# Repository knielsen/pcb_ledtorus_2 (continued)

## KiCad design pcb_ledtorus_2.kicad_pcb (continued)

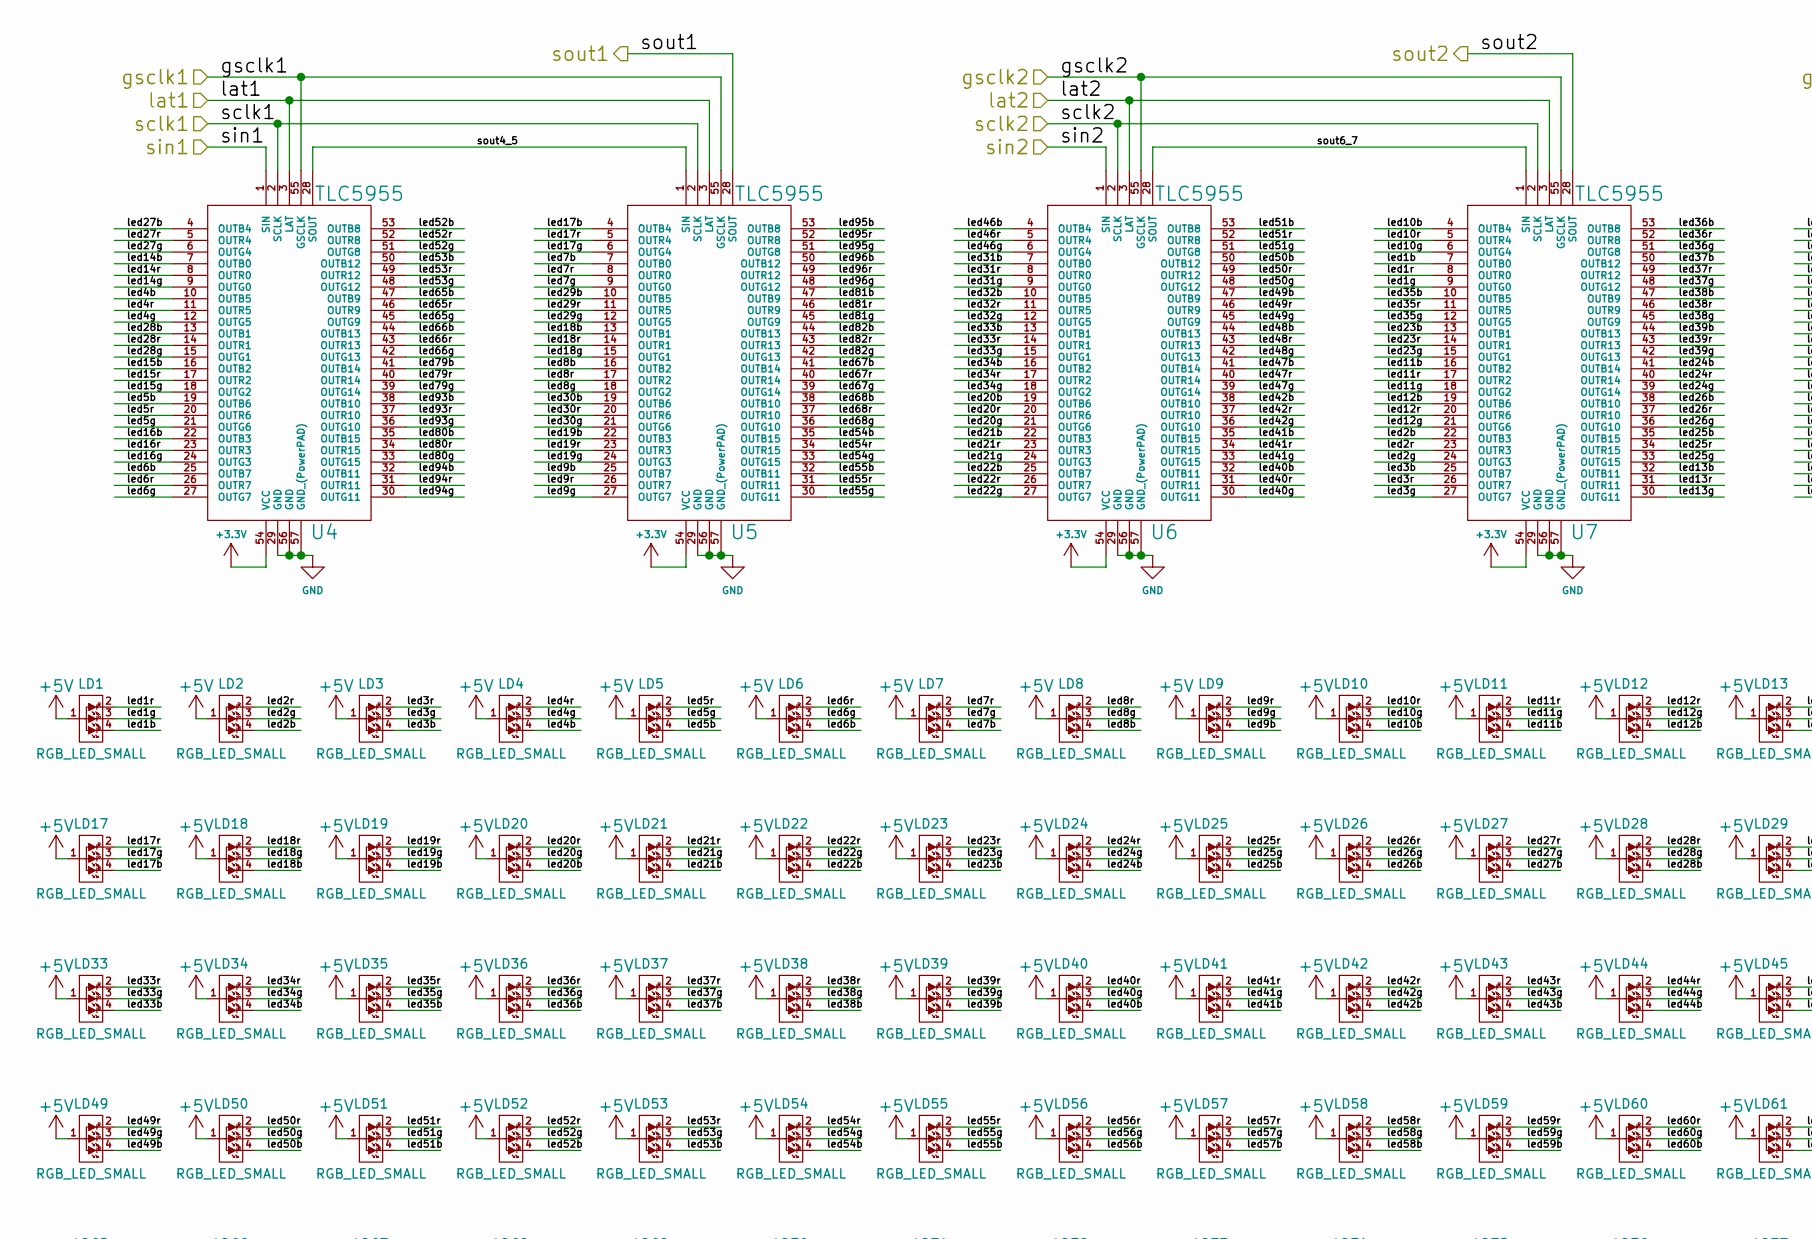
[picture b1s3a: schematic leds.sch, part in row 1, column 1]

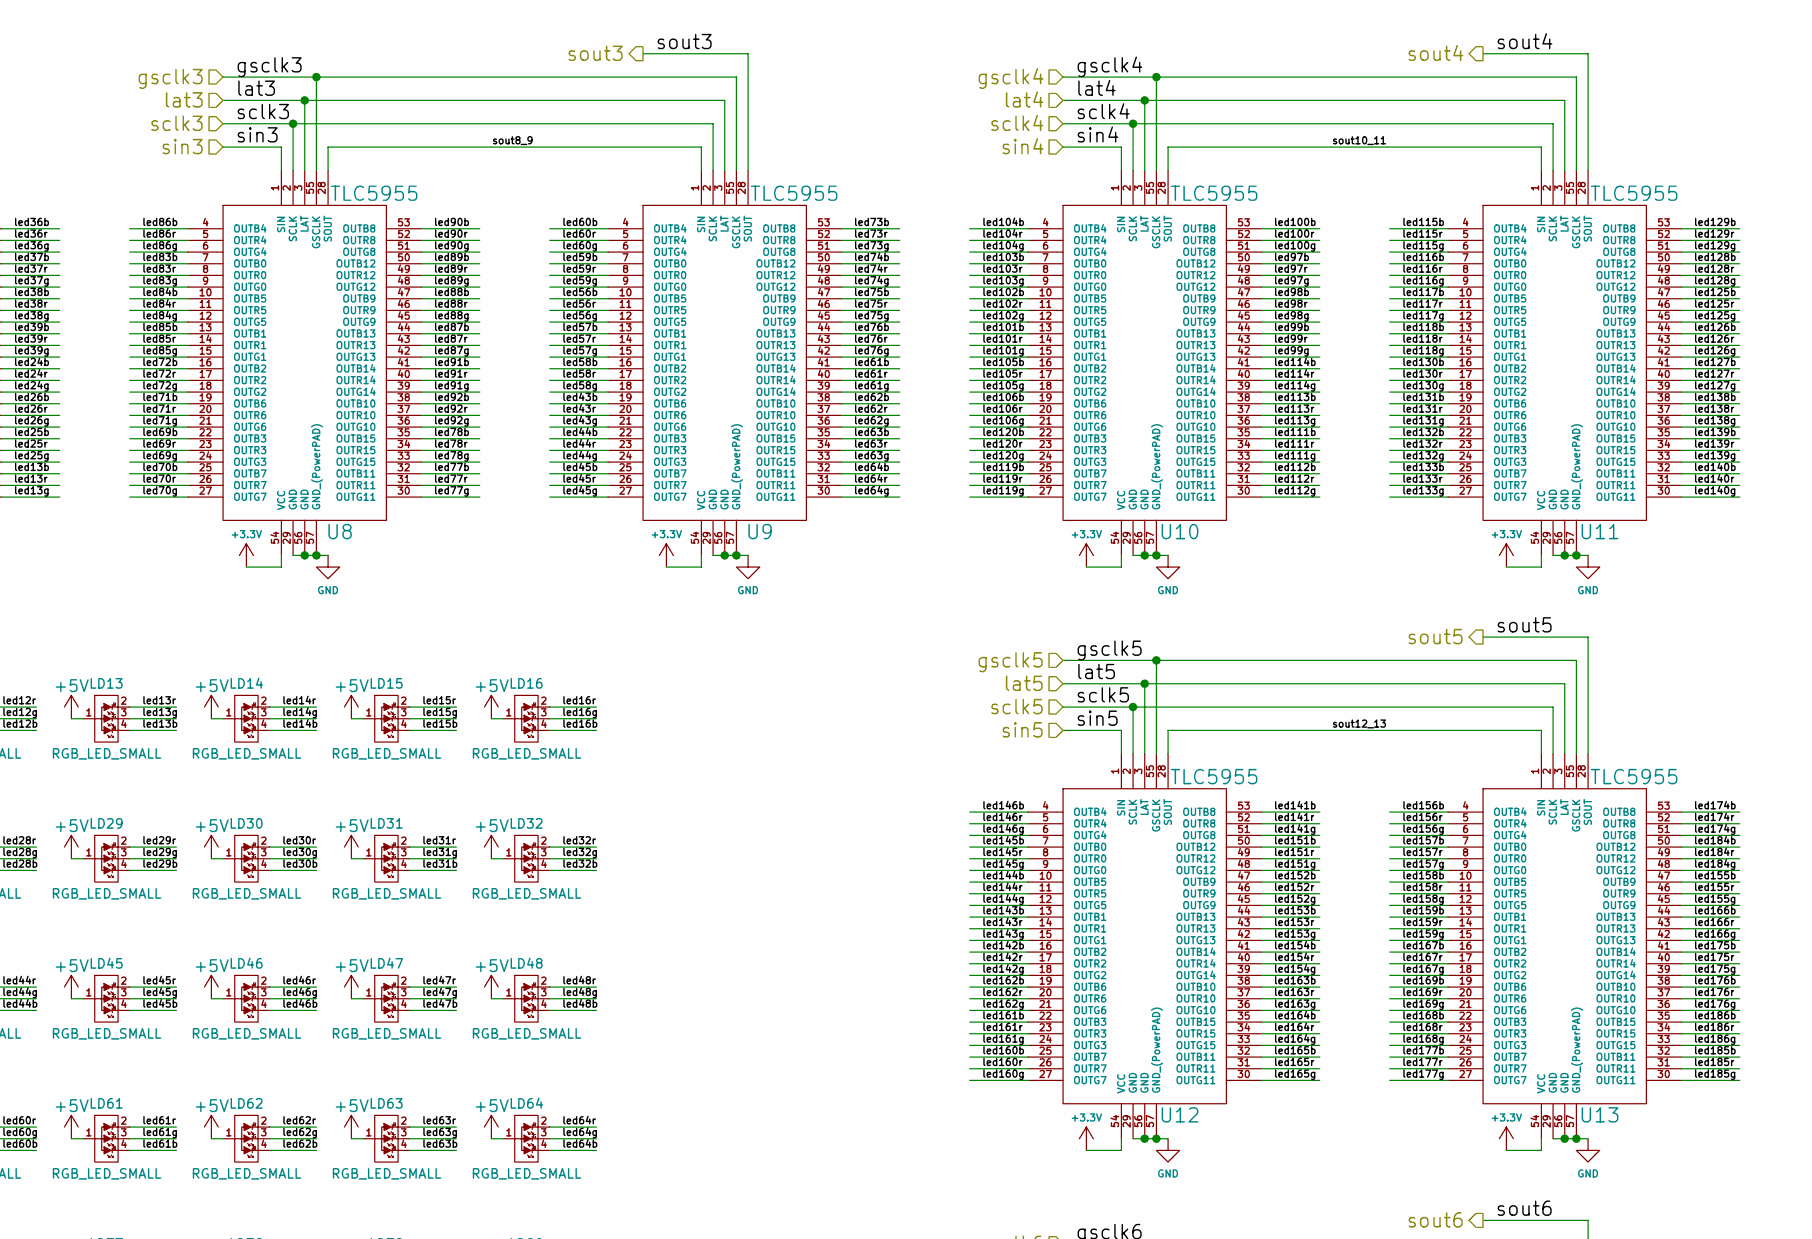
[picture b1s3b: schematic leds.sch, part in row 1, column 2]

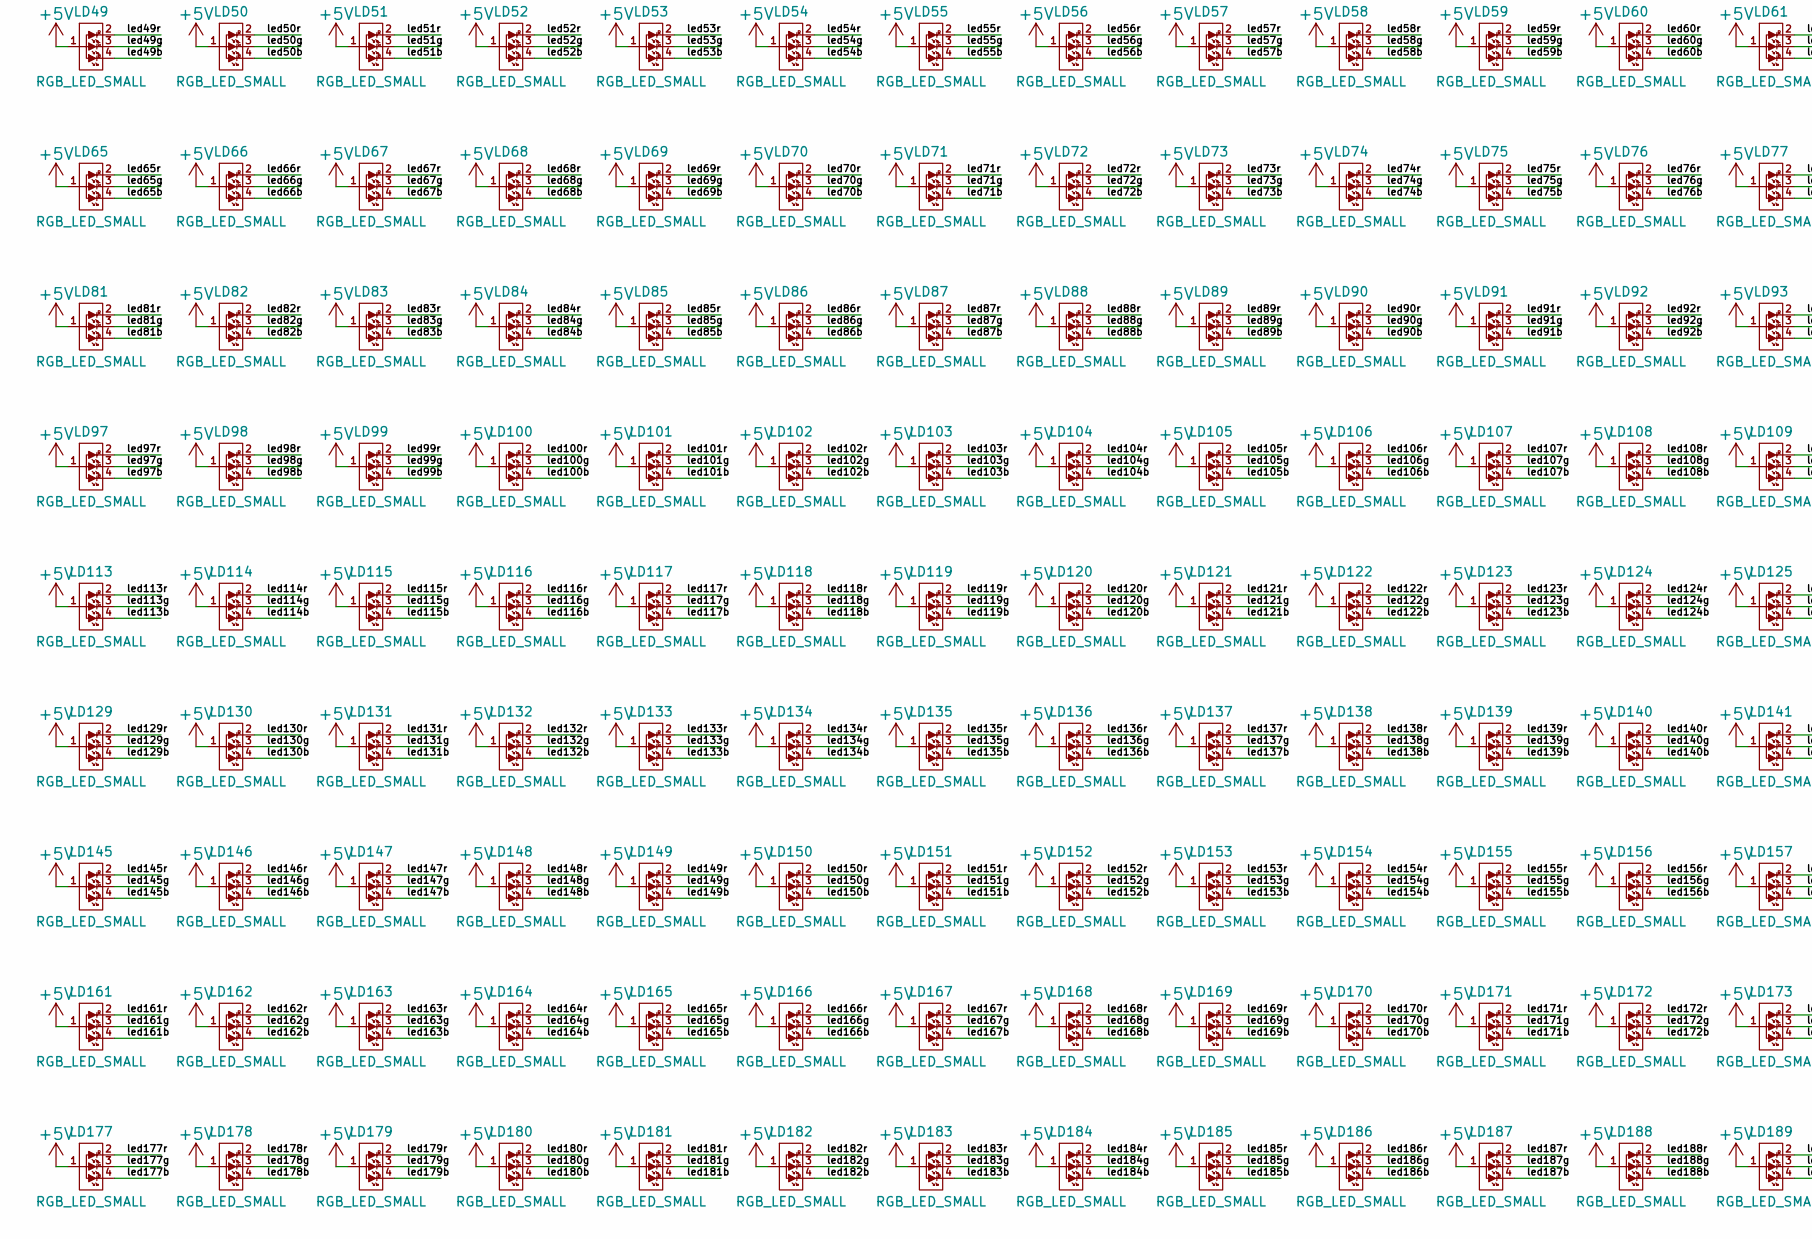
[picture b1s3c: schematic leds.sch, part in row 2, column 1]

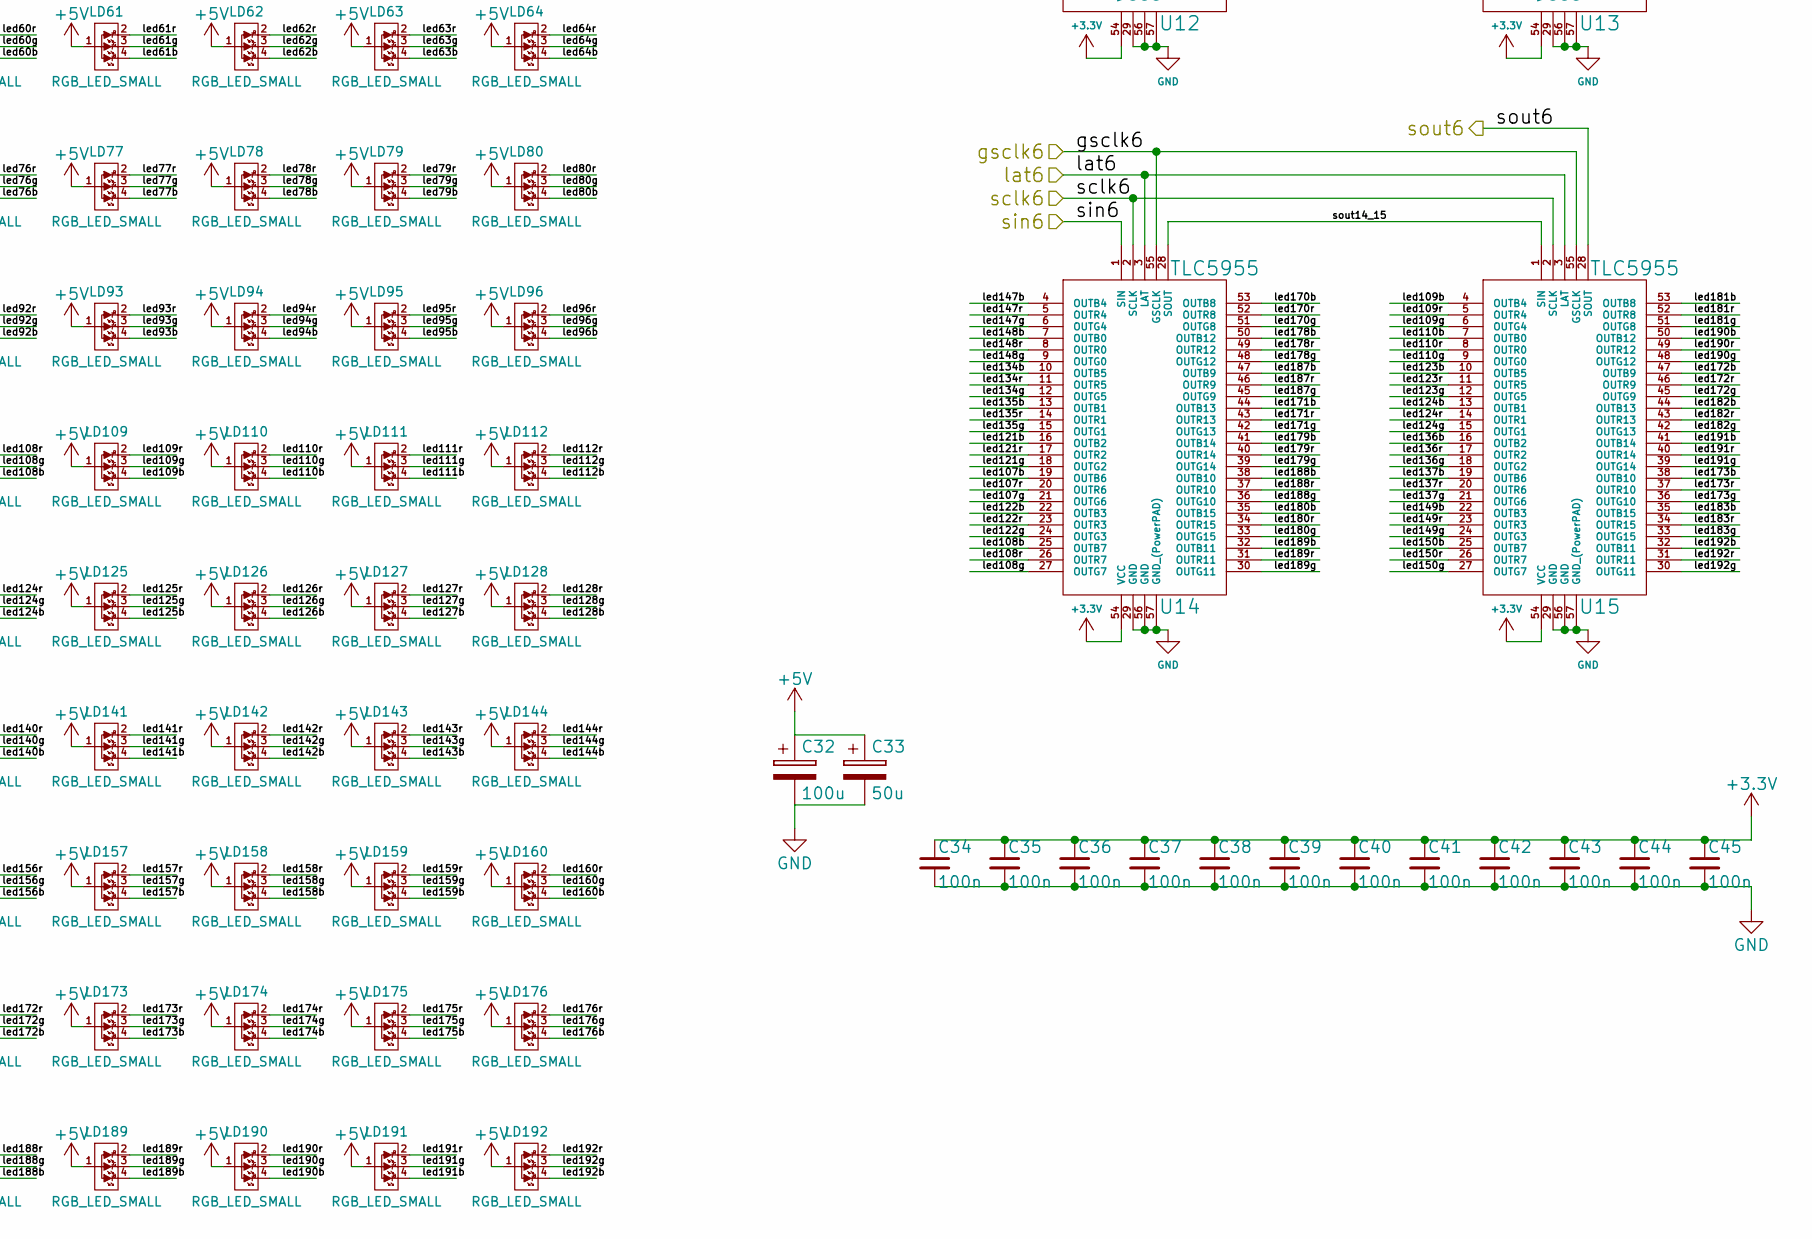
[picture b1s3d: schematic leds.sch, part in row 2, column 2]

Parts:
C32: 100u; c_elec_6.3x5.8
C33: 50u; c_elec_6.3x5.8
C34, C35, C36, C37, C38, C39, C40, C41, C42, C43, C44, C45: 100n; c_0603
LD1, LD2, LD3, LD4, LD5, LD6, LD7, LD8, LD9, LD10, LD11, LD12, LD13, LD14, LD15, LD16, LD17, LD18, LD19, LD20, LD21, LD22, LD23, LD24, LD25, LD26, LD27, LD28, LD29, LD30, LD31, LD32, LD33, LD34, LD35, LD36, LD37, LD38, LD39, LD40, LD41, LD42, LD43, LD44, LD45, LD46, LD47, LD48, LD49, LD50, LD51, LD52, LD53, LD54, LD55, LD56, LD57, LD58, LD59, LD60, LD61, LD62, LD63, LD64, LD65, LD66, LD67, LD68, LD69, LD70, LD71, LD72, LD73, LD74, LD75, LD76, LD77, LD78, LD79, LD80, LD81, LD82, LD83, LD84, LD85, LD86, LD87, LD88, LD89, LD90, LD91, LD92, LD93, LD94, LD95, LD96, LD97, LD98, LD99, LD100, LD101, LD102, LD103, LD104, LD105, LD106, LD107, LD108, LD109, LD110, LD111, LD112, LD113, LD114, LD115, LD116, LD117, LD118, LD119, LD120, LD121, LD122, LD123, LD124, LD125, LD126, LD127, LD128, LD129, LD130, LD131, LD132, LD133, LD134, LD135, LD136, LD137, LD138, LD139, LD140, LD141, LD142, LD143, LD144, LD145, LD146, LD147, LD148, LD149, LD150, LD151, LD152, LD153, LD154, LD155, LD156, LD157, LD158, LD159, LD160, LD161, LD162, LD163, LD164, LD165, LD166, LD167, LD168, LD169, LD170, LD171, LD172, LD173, LD174, LD175, LD176, LD177, LD178, LD179, LD180, LD181, LD182, LD183, LD184, LD185, LD186, LD187, LD188, LD189, LD190, LD191, LD192: RGB_LED_SMALL; RGB_0603
U4, U5, U6, U7, U8, U9, U10, U11, U12, U13, U14, U15: TLC5955; TLC5955DCA

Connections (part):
+5V: C32.1, C33.1, LD1.1 (AG), LD2.1 (AG), LD3.1 (AG), LD4.1 (AG), LD5.1 (AG), LD6.1 (AG), LD7.1 (AG), LD8.1 (AG), LD9.1 (AG), LD10.1 (AG), LD11.1 (AG), LD12.1 (AG), LD13.1 (AG), LD14.1 (AG), LD15.1 (AG), LD16.1 (AG), LD17.1 (AG), LD18.1 (AG), LD19.1 (AG), LD20.1 (AG), LD21.1 (AG), LD22.1 (AG), LD23.1 (AG), LD24.1 (AG), LD25.1 (AG), LD26.1 (AG), LD27.1 (AG), LD28.1 (AG), LD29.1 (AG), LD30.1 (AG), LD31.1 (AG), LD32.1 (AG), LD33.1 (AG), LD34.1 (AG), LD35.1 (AG), LD36.1 (AG), LD37.1 (AG), LD38.1 (AG), LD39.1 (AG), LD40.1 (AG), LD41.1 (AG), LD42.1 (AG), LD43.1 (AG), LD44.1 (AG), LD45.1 (AG), LD46.1 (AG), LD47.1 (AG), LD48.1 (AG), LD49.1 (AG), LD50.1 (AG), LD51.1 (AG), LD52.1 (AG), LD53.1 (AG), LD54.1 (AG), LD55.1 (AG), LD56.1 (AG), LD57.1 (AG), LD58.1 (AG), LD59.1 (AG), LD60.1 (AG), LD61.1 (AG), LD62.1 (AG), LD63.1 (AG), LD64.1 (AG), LD65.1 (AG), LD66.1 (AG), LD67.1 (AG), LD68.1 (AG), LD69.1 (AG), LD70.1 (AG), LD71.1 (AG), LD72.1 (AG), LD73.1 (AG), LD74.1 (AG), LD75.1 (AG), LD76.1 (AG), LD77.1 (AG), LD78.1 (AG), LD79.1 (AG)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; also elsewhere on the board
/LEDs/led1b: LD1.4 (R), U7.7 (OUTB0)
/LEDs/led1g: LD1.3 (R), U7.9 (OUTG0)
/LEDs/led1r: LD1.2 (R), U7.8 (OUTR0)
/LEDs/led2b: LD2.4 (R), U7.22 (OUTB3)
/LEDs/led2g: LD2.3 (R), U7.24 (OUTG3)
/LEDs/led2r: LD2.2 (R), U7.23 (OUTR3)
/LEDs/led3b: LD3.4 (R), U7.25 (OUTB7)
/LEDs/led3g: LD3.3 (R), U7.27 (OUTG7)
/LEDs/led3r: LD3.2 (R), U7.26 (OUTR7)
/LEDs/led4b: LD4.4 (R), U4.10 (OUTB5)
/LEDs/led4g: LD4.3 (R), U4.12 (OUTG5)
/LEDs/led4r: LD4.2 (R), U4.11 (OUTR5)
/LEDs/led5b: LD5.4 (R), U4.19 (OUTB6)
/LEDs/led5g: LD5.3 (R), U4.21 (OUTG6)
/LEDs/led5r: LD5.2 (R), U4.20 (OUTR6)
/LEDs/led6b: LD6.4 (R), U4.25 (OUTB7)
/LEDs/led6g: LD6.3 (R), U4.27 (OUTG7)
/LEDs/led6r: LD6.2 (R), U4.26 (OUTR7)
/LEDs/led7b: LD7.4 (R), U5.7 (OUTB0)
/LEDs/led7g: LD7.3 (R), U5.9 (OUTG0)
/LEDs/led7r: LD7.2 (R), U5.8 (OUTR0)
/LEDs/led8b: LD8.4 (R), U5.16 (OUTB2)
/LEDs/led8g: LD8.3 (R), U5.18 (OUTG2)
/LEDs/led8r: LD8.2 (R), U5.17 (OUTR2)
/LEDs/led9b: LD9.4 (R), U5.25 (OUTB7)
/LEDs/led9g: LD9.3 (R), U5.27 (OUTG7)
/LEDs/led9r: LD9.2 (R), U5.26 (OUTR7)
/LEDs/led10b: LD10.4 (R), U7.4 (OUTB4)
/LEDs/led10g: LD10.3 (R), U7.6 (OUTG4)
/LEDs/led10r: LD10.2 (R), U7.5 (OUTR4)
/LEDs/led11b: LD11.4 (R), U7.16 (OUTB2)
/LEDs/led11g: LD11.3 (R), U7.18 (OUTG2)
/LEDs/led11r: LD11.2 (R), U7.17 (OUTR2)
/LEDs/led12b: LD12.4 (R), U7.19 (OUTB6)
/LEDs/led12g: LD12.3 (R), U7.21 (OUTG6)
/LEDs/led12r: LD12.2 (R), U7.20 (OUTR6)
/LEDs/led13b: LD13.4 (R), U7.32 (OUTB11)
/LEDs/led13g: LD13.3 (R), U7.30 (OUTG11)
/LEDs/led13r: LD13.2 (R), U7.31 (OUTR11)
/LEDs/led14b: LD14.4 (R), U4.7 (OUTB0)
/LEDs/led14g: LD14.3 (R), U4.9 (OUTG0)
/LEDs/led14r: LD14.2 (R), U4.8 (OUTR0)
/LEDs/led15b: LD15.4 (R), U4.16 (OUTB2)
/LEDs/led15g: LD15.3 (R), U4.18 (OUTG2)
/LEDs/led15r: LD15.2 (R), U4.17 (OUTR2)
/LEDs/led16b: LD16.4 (R), U4.22 (OUTB3)
/LEDs/led16g: LD16.3 (R), U4.24 (OUTG3)
/LEDs/led16r: LD16.2 (R), U4.23 (OUTR3)
/LEDs/led17b: LD17.4 (R), U5.4 (OUTB4)
/LEDs/led17g: LD17.3 (R), U5.6 (OUTG4)
/LEDs/led17r: LD17.2 (R), U5.5 (OUTR4)
/LEDs/led18b: LD18.4 (R), U5.13 (OUTB1)
/LEDs/led18g: LD18.3 (R), U5.15 (OUTG1)
/LEDs/led18r: LD18.2 (R), U5.14 (OUTR1)
/LEDs/led19b: LD19.4 (R), U5.22 (OUTB3)
/LEDs/led19g: LD19.3 (R), U5.24 (OUTG3)
/LEDs/led19r: LD19.2 (R), U5.23 (OUTR3)
/LEDs/led20b: LD20.4 (R), U6.19 (OUTB6)
/LEDs/led20g: LD20.3 (R), U6.21 (OUTG6)
/LEDs/led20r: LD20.2 (R), U6.20 (OUTR6)
/LEDs/led21b: LD21.4 (R), U6.22 (OUTB3)
/LEDs/led21g: LD21.3 (R), U6.24 (OUTG3)
/LEDs/led21r: LD21.2 (R), U6.23 (OUTR3)
/LEDs/led22b: LD22.4 (R), U6.25 (OUTB7)
/LEDs/led22g: LD22.3 (R), U6.27 (OUTG7)
/LEDs/led22r: LD22.2 (R), U6.26 (OUTR7)
/LEDs/led23b: LD23.4 (R), U7.13 (OUTB1)
/LEDs/led23g: LD23.3 (R), U7.15 (OUTG1)
/LEDs/led23r: LD23.2 (R), U7.14 (OUTR1)
/LEDs/led24b: LD24.4 (R), U7.41 (OUTB14)
/LEDs/led24g: LD24.3 (R), U7.39 (OUTG14)
/LEDs/led24r: LD24.2 (R), U7.40 (OUTR14)
/LEDs/led25b: LD25.4 (R), U7.35 (OUTB15)
/LEDs/led25g: LD25.3 (R), U7.33 (OUTG15)
/LEDs/led25r: LD25.2 (R), U7.34 (OUTR15)
/LEDs/led26b: LD26.4 (R), U7.38 (OUTB10)
/LEDs/led26g: LD26.3 (R), U7.36 (OUTG10)
/LEDs/led26r: LD26.2 (R), U7.37 (OUTR10)
/LEDs/led27b: LD27.4 (R), U4.4 (OUTB4)
/LEDs/led27g: LD27.3 (R), U4.6 (OUTG4)
/LEDs/led27r: LD27.2 (R), U4.5 (OUTR4)
/LEDs/led28b: LD28.4 (R), U4.13 (OUTB1)
/LEDs/led28g: LD28.3 (R), U4.15 (OUTG1)
/LEDs/led28r: LD28.2 (R), U4.14 (OUTR1)
/LEDs/led29b: LD29.4 (R), U5.10 (OUTB5)
/LEDs/led29g: LD29.3 (R), U5.12 (OUTG5)
/LEDs/led29r: LD29.2 (R), U5.11 (OUTR5)
/LEDs/led30b: LD30.4 (R), U5.19 (OUTB6)
/LEDs/led30g: LD30.3 (R), U5.21 (OUTG6)
/LEDs/led30r: LD30.2 (R), U5.20 (OUTR6)
/LEDs/led31b: LD31.4 (R), U6.7 (OUTB0)
/LEDs/led31g: LD31.3 (R), U6.9 (OUTG0)
/LEDs/led31r: LD31.2 (R), U6.8 (OUTR0)
/LEDs/led32b: LD32.4 (R), U6.10 (OUTB5)
/LEDs/led32g: LD32.3 (R), U6.12 (OUTG5)
/LEDs/led32r: LD32.2 (R), U6.11 (OUTR5)
/LEDs/led33b: LD33.4 (R), U6.13 (OUTB1)
/LEDs/led33g: LD33.3 (R), U6.15 (OUTG1)
/LEDs/led33r: LD33.2 (R), U6.14 (OUTR1)
/LEDs/led34b: LD34.4 (R), U6.16 (OUTB2)
/LEDs/led34g: LD34.3 (R), U6.18 (OUTG2)
/LEDs/led34r: LD34.2 (R), U6.17 (OUTR2)
/LEDs/led35b: LD35.4 (R), U7.10 (OUTB5)
/LEDs/led35g: LD35.3 (R), U7.12 (OUTG5)
/LEDs/led35r: LD35.2 (R), U7.11 (OUTR5)
/LEDs/led36b: LD36.4 (R), U7.53 (OUTB8)
/LEDs/led36g: LD36.3 (R), U7.51 (OUTG8)
/LEDs/led36r: LD36.2 (R), U7.52 (OUTR8)
/LEDs/led37b: LD37.4 (R), U7.50 (OUTB12)
/LEDs/led37g: LD37.3 (R), U7.48 (OUTG12)
/LEDs/led37r: LD37.2 (R), U7.49 (OUTR12)
/LEDs/led38b: LD38.4 (R), U7.47 (OUTB9)
/LEDs/led38g: LD38.3 (R), U7.45 (OUTG9)
/LEDs/led38r: LD38.2 (R), U7.46 (OUTR9)
/LEDs/led39b: LD39.4 (R), U7.44 (OUTB13)
/LEDs/led39g: LD39.3 (R), U7.42 (OUTG13)
/LEDs/led39r: LD39.2 (R), U7.43 (OUTR13)
/LEDs/led40b: LD40.4 (R), U6.32 (OUTB11)
/LEDs/led40g: LD40.3 (R), U6.30 (OUTG11)
/LEDs/led40r: LD40.2 (R), U6.31 (OUTR11)
/LEDs/led41b: LD41.4 (R), U6.35 (OUTB15)
/LEDs/led41g: LD41.3 (R), U6.33 (OUTG15)
/LEDs/led41r: LD41.2 (R), U6.34 (OUTR15)
/LEDs/led42b: LD42.4 (R), U6.38 (OUTB10)
/LEDs/led42g: LD42.3 (R), U6.36 (OUTG10)
/LEDs/led42r: LD42.2 (R), U6.37 (OUTR10)
/LEDs/led43b: LD43.4 (R), U9.19 (OUTB6)
/LEDs/led43g: LD43.3 (R), U9.21 (OUTG6)
/LEDs/led43r: LD43.2 (R), U9.20 (OUTR6)
/LEDs/led44b: LD44.4 (R), U9.22 (OUTB3)
/LEDs/led44g: LD44.3 (R), U9.24 (OUTG3)
/LEDs/led44r: LD44.2 (R), U9.23 (OUTR3)
/LEDs/led45b: LD45.4 (R), U9.25 (OUTB7)
/LEDs/led45g: LD45.3 (R), U9.27 (OUTG7)
/LEDs/led45r: LD45.2 (R), U9.26 (OUTR7)
/LEDs/led46b: LD46.4 (R), U6.4 (OUTB4)
/LEDs/led46g: LD46.3 (R), U6.6 (OUTG4)
/LEDs/led46r: LD46.2 (R), U6.5 (OUTR4)
/LEDs/led47b: LD47.4 (R), U6.41 (OUTB14)
/LEDs/led47g: LD47.3 (R), U6.39 (OUTG14)
/LEDs/led47r: LD47.2 (R), U6.40 (OUTR14)
/LEDs/led48b: LD48.4 (R), U6.44 (OUTB13)
/LEDs/led48g: LD48.3 (R), U6.42 (OUTG13)
/LEDs/led48r: LD48.2 (R), U6.43 (OUTR13)
/LEDs/led49b: LD49.4 (R), U6.47 (OUTB9)
/LEDs/led49g: LD49.3 (R), U6.45 (OUTG9)
/LEDs/led49r: LD49.2 (R), U6.46 (OUTR9)
/LEDs/led50b: LD50.4 (R), U6.50 (OUTB12)
/LEDs/led50g: LD50.3 (R), U6.48 (OUTG12)
/LEDs/led50r: LD50.2 (R), U6.49 (OUTR12)
/LEDs/led51b: LD51.4 (R), U6.53 (OUTB8)
/LEDs/led51g: LD51.3 (R), U6.51 (OUTG8)
/LEDs/led51r: LD51.2 (R), U6.52 (OUTR8)
/LEDs/led52b: LD52.4 (R), U4.53 (OUTB8)
/LEDs/led52g: LD52.3 (R), U4.51 (OUTG8)
/LEDs/led52r: LD52.2 (R), U4.52 (OUTR8)
/LEDs/led53b: LD53.4 (R), U4.50 (OUTB12)
/LEDs/led53g: LD53.3 (R), U4.48 (OUTG12)
/LEDs/led53r: LD53.2 (R), U4.49 (OUTR12)
/LEDs/led54b: LD54.4 (R), U5.35 (OUTB15)
/LEDs/led54g: LD54.3 (R), U5.33 (OUTG15)
/LEDs/led54r: LD54.2 (R), U5.34 (OUTR15)
/LEDs/led55b: LD55.4 (R), U5.32 (OUTB11)
/LEDs/led55g: LD55.3 (R), U5.30 (OUTG11)
/LEDs/led55r: LD55.2 (R), U5.31 (OUTR11)
/LEDs/led56b: LD56.4 (R), U9.10 (OUTB5)
/LEDs/led56g: LD56.3 (R), U9.12 (OUTG5)
/LEDs/led56r: LD56.2 (R), U9.11 (OUTR5)
/LEDs/led57b: LD57.4 (R), U9.13 (OUTB1)
/LEDs/led57g: LD57.3 (R), U9.15 (OUTG1)
/LEDs/led57r: LD57.2 (R), U9.14 (OUTR1)
/LEDs/led58b: LD58.4 (R), U9.16 (OUTB2)
/LEDs/led58g: LD58.3 (R), U9.18 (OUTG2)
/LEDs/led58r: LD58.2 (R), U9.17 (OUTR2)
/LEDs/led59b: LD59.4 (R), U9.7 (OUTB0)
/LEDs/led59g: LD59.3 (R), U9.9 (OUTG0)
/LEDs/led59r: LD59.2 (R), U9.8 (OUTR0)
/LEDs/led60b: LD60.4 (R), U9.4 (OUTB4)
/LEDs/led60g: LD60.3 (R), U9.6 (OUTG4)
/LEDs/led60r: LD60.2 (R), U9.5 (OUTR4)
/LEDs/led61b: LD61.4 (R), U9.41 (OUTB14)
/LEDs/led61g: LD61.3 (R), U9.39 (OUTG14)
/LEDs/led61r: LD61.2 (R), U9.40 (OUTR14)
/LEDs/led62b: LD62.4 (R), U9.38 (OUTB10)
/LEDs/led62g: LD62.3 (R), U9.36 (OUTG10)
/LEDs/led62r: LD62.2 (R), U9.37 (OUTR10)
/LEDs/led63b: LD63.4 (R), U9.35 (OUTB15)
/LEDs/led63g: LD63.3 (R), U9.33 (OUTG15)
/LEDs/led63r: LD63.2 (R), U9.34 (OUTR15)
/LEDs/led64b: LD64.4 (R), U9.32 (OUTB11)
/LEDs/led64g: LD64.3 (R), U9.30 (OUTG11)
/LEDs/led64r: LD64.2 (R), U9.31 (OUTR11)
/LEDs/led65b: LD65.4 (R), U4.47 (OUTB9)
/LEDs/led65g: LD65.3 (R), U4.45 (OUTG9)
/LEDs/led65r: LD65.2 (R), U4.46 (OUTR9)
/LEDs/led66b: LD66.4 (R), U4.44 (OUTB13)
/LEDs/led66g: LD66.3 (R), U4.42 (OUTG13)
/LEDs/led66r: LD66.2 (R), U4.43 (OUTR13)
/LEDs/led67b: LD67.4 (R), U5.41 (OUTB14)
/LEDs/led67g: LD67.3 (R), U5.39 (OUTG14)
/LEDs/led67r: LD67.2 (R), U5.40 (OUTR14)
/LEDs/led68b: LD68.4 (R), U5.38 (OUTB10)
/LEDs/led68g: LD68.3 (R), U5.36 (OUTG10)
/LEDs/led68r: LD68.2 (R), U5.37 (OUTR10)
/LEDs/led69b: LD69.4 (R), U8.22 (OUTB3)
/LEDs/led69g: LD69.3 (R), U8.24 (OUTG3)
/LEDs/led69r: LD69.2 (R), U8.23 (OUTR3)
/LEDs/led70b: LD70.4 (R), U8.25 (OUTB7)
/LEDs/led70g: LD70.3 (R), U8.27 (OUTG7)
/LEDs/led70r: LD70.2 (R), U8.26 (OUTR7)
/LEDs/led71b: LD71.4 (R), U8.19 (OUTB6)
/LEDs/led71g: LD71.3 (R), U8.21 (OUTG6)
/LEDs/led71r: LD71.2 (R), U8.20 (OUTR6)
/LEDs/led72b: LD72.4 (R), U8.16 (OUTB2)
/LEDs/led72g: LD72.3 (R), U8.18 (OUTG2)
/LEDs/led72r: LD72.2 (R), U8.17 (OUTR2)
/LEDs/led73b: LD73.4 (R), U9.53 (OUTB8)
/LEDs/led73g: LD73.3 (R), U9.51 (OUTG8)
/LEDs/led73r: LD73.2 (R), U9.52 (OUTR8)
/LEDs/led74b: LD74.4 (R), U9.50 (OUTB12)
/LEDs/led74g: LD74.3 (R), U9.48 (OUTG12)
/LEDs/led74r: LD74.2 (R), U9.49 (OUTR12)
/LEDs/led75b: LD75.4 (R), U9.47 (OUTB9)
/LEDs/led75g: LD75.3 (R), U9.45 (OUTG9)
/LEDs/led75r: LD75.2 (R), U9.46 (OUTR9)
/LEDs/led76b: LD76.4 (R), U9.44 (OUTB13)
/LEDs/led76g: LD76.3 (R), U9.42 (OUTG13)
/LEDs/led76r: LD76.2 (R), U9.43 (OUTR13)
/LEDs/led77b: LD77.4 (R), U8.32 (OUTB11)
/LEDs/led77g: LD77.3 (R), U8.30 (OUTG11)
/LEDs/led77r: LD77.2 (R), U8.31 (OUTR11)
/LEDs/led78b: LD78.4 (R), U8.35 (OUTB15)
/LEDs/led78g: LD78.3 (R), U8.33 (OUTG15)
/LEDs/led78r: LD78.2 (R), U8.34 (OUTR15)
/LEDs/led79b: LD79.4 (R), U4.41 (OUTB14)
/LEDs/led79g: LD79.3 (R), U4.39 (OUTG14)
/LEDs/led79r: LD79.2 (R), U4.40 (OUTR14)
/LEDs/led80b: LD80.4 (R), U4.35 (OUTB15)
/LEDs/led80g: LD80.3 (R), U4.33 (OUTG15)
/LEDs/led80r: LD80.2 (R), U4.34 (OUTR15)
/LEDs/led81b: LD81.4 (R), U5.47 (OUTB9)
/LEDs/led81g: LD81.3 (R), U5.45 (OUTG9)
/LEDs/led81r: LD81.2 (R), U5.46 (OUTR9)
/LEDs/led82b: LD82.4 (R), U5.44 (OUTB13)
/LEDs/led82g: LD82.3 (R), U5.42 (OUTG13)
/LEDs/led82r: LD82.2 (R), U5.43 (OUTR13)
/LEDs/led83b: LD83.4 (R), U8.7 (OUTB0)
/LEDs/led83g: LD83.3 (R), U8.9 (OUTG0)
/LEDs/led83r: LD83.2 (R), U8.8 (OUTR0)
/LEDs/led84b: LD84.4 (R), U8.10 (OUTB5)
/LEDs/led84g: LD84.3 (R), U8.12 (OUTG5)
/LEDs/led84r: LD84.2 (R), U8.11 (OUTR5)
/LEDs/led85b: LD85.4 (R), U8.13 (OUTB1)
/LEDs/led85g: LD85.3 (R), U8.15 (OUTG1)
/LEDs/led85r: LD85.2 (R), U8.14 (OUTR1)
/LEDs/led86b: LD86.4 (R), U8.4 (OUTB4)
/LEDs/led86g: LD86.3 (R), U8.6 (OUTG4)
/LEDs/led86r: LD86.2 (R), U8.5 (OUTR4)
/LEDs/led87b: LD87.4 (R), U8.44 (OUTB13)
/LEDs/led87g: LD87.3 (R), U8.42 (OUTG13)
/LEDs/led87r: LD87.2 (R), U8.43 (OUTR13)
/LEDs/led88b: LD88.4 (R), U8.47 (OUTB9)
/LEDs/led88g: LD88.3 (R), U8.45 (OUTG9)
/LEDs/led88r: LD88.2 (R), U8.46 (OUTR9)
/LEDs/led89b: LD89.4 (R), U8.50 (OUTB12)
/LEDs/led89g: LD89.3 (R), U8.48 (OUTG12)
/LEDs/led89r: LD89.2 (R), U8.49 (OUTR12)
/LEDs/led90b: LD90.4 (R), U8.53 (OUTB8)
/LEDs/led90g: LD90.3 (R), U8.51 (OUTG8)
/LEDs/led90r: LD90.2 (R), U8.52 (OUTR8)
/LEDs/led91b: LD91.4 (R), U8.41 (OUTB14)
/LEDs/led91g: LD91.3 (R), U8.39 (OUTG14)
/LEDs/led91r: LD91.2 (R), U8.40 (OUTR14)
/LEDs/led92b: LD92.4 (R), U8.38 (OUTB10)
/LEDs/led92g: LD92.3 (R), U8.36 (OUTG10)
/LEDs/led92r: LD92.2 (R), U8.37 (OUTR10)
/LEDs/led93b: LD93.4 (R), U4.38 (OUTB10)
/LEDs/led93g: LD93.3 (R), U4.36 (OUTG10)
/LEDs/led93r: LD93.2 (R), U4.37 (OUTR10)
/LEDs/led94b: LD94.4 (R), U4.32 (OUTB11)
/LEDs/led94g: LD94.3 (R), U4.30 (OUTG11)
/LEDs/led94r: LD94.2 (R), U4.31 (OUTR11)
/LEDs/led95b: LD95.4 (R), U5.53 (OUTB8)
/LEDs/led95g: LD95.3 (R), U5.51 (OUTG8)
/LEDs/led95r: LD95.2 (R), U5.52 (OUTR8)
/LEDs/led96b: LD96.4 (R), U5.50 (OUTB12)
/LEDs/led96g: LD96.3 (R), U5.48 (OUTG12)
/LEDs/led96r: LD96.2 (R), U5.49 (OUTR12)
/LEDs/led97b: LD97.4 (R), U10.50 (OUTB12)
/LEDs/led97g: LD97.3 (R), U10.48 (OUTG12)
/LEDs/led97r: LD97.2 (R), U10.49 (OUTR12)
/LEDs/led98b: LD98.4 (R), U10.47 (OUTB9)
/LEDs/led98g: LD98.3 (R), U10.45 (OUTG9)
/LEDs/led98r: LD98.2 (R), U10.46 (OUTR9)
/LEDs/led99b: LD99.4 (R), U10.44 (OUTB13)
/LEDs/led99g: LD99.3 (R), U10.42 (OUTG13)
/LEDs/led99r: LD99.2 (R), U10.43 (OUTR13)
/LEDs/led100b: LD100.4 (R), U10.53 (OUTB8)
/LEDs/led100g: LD100.3 (R), U10.51 (OUTG8)
/LEDs/led100r: LD100.2 (R), U10.52 (OUTR8)
/LEDs/led101b: LD101.4 (R), U10.13 (OUTB1)
/LEDs/led101g: LD101.3 (R), U10.15 (OUTG1)
/LEDs/led101r: LD101.2 (R), U10.14 (OUTR1)
/LEDs/led102b: LD102.4 (R), U10.10 (OUTB5)
/LEDs/led102g: LD102.3 (R), U10.12 (OUTG5)
/LEDs/led102r: LD102.2 (R), U10.11 (OUTR5)
/LEDs/led103b: LD103.4 (R), U10.7 (OUTB0)
/LEDs/led103g: LD103.3 (R), U10.9 (OUTG0)
/LEDs/led103r: LD103.2 (R), U10.8 (OUTR0)
/LEDs/led104b: LD104.4 (R), U10.4 (OUTB4)
/LEDs/led104g: LD104.3 (R), U10.6 (OUTG4)
/LEDs/led104r: LD104.2 (R), U10.5 (OUTR4)
/LEDs/led105b: LD105.4 (R), U10.16 (OUTB2)
/LEDs/led105g: LD105.3 (R), U10.18 (OUTG2)
/LEDs/led105r: LD105.2 (R), U10.17 (OUTR2)
/LEDs/led106b: LD106.4 (R), U10.19 (OUTB6)
/LEDs/led106g: LD106.3 (R), U10.21 (OUTG6)
/LEDs/led106r: LD106.2 (R), U10.20 (OUTR6)
/LEDs/led107b: LD107.4 (R), U14.19 (OUTB6)
/LEDs/led107g: LD107.3 (R), U14.21 (OUTG6)
/LEDs/led107r: LD107.2 (R), U14.20 (OUTR6)
/LEDs/led108b: LD108.4 (R), U14.25 (OUTB7)
/LEDs/led108g: LD108.3 (R), U14.27 (OUTG7)
/LEDs/led108r: LD108.2 (R), U14.26 (OUTR7)
/LEDs/led109b: LD109.4 (R), U15.4 (OUTB4)
/LEDs/led109g: LD109.3 (R), U15.6 (OUTG4)
/LEDs/led109r: LD109.2 (R), U15.5 (OUTR4)
/LEDs/led110b: LD110.4 (R), U15.7 (OUTB0)
/LEDs/led110g: LD110.3 (R), U15.9 (OUTG0)
/LEDs/led110r: LD110.2 (R), U15.8 (OUTR0)
/LEDs/led111b: LD111.4 (R), U10.35 (OUTB15)
/LEDs/led111g: LD111.3 (R), U10.33 (OUTG15)
/LEDs/led111r: LD111.2 (R), U10.34 (OUTR15)
/LEDs/led112b: LD112.4 (R), U10.32 (OUTB11)
/LEDs/led112g: LD112.3 (R), U10.30 (OUTG11)
/LEDs/led112r: LD112.2 (R), U10.31 (OUTR11)
/LEDs/led113b: LD113.4 (R), U10.38 (OUTB10)
/LEDs/led113g: LD113.3 (R), U10.36 (OUTG10)
/LEDs/led113r: LD113.2 (R), U10.37 (OUTR10)
/LEDs/led114b: LD114.4 (R), U10.41 (OUTB14)
/LEDs/led114g: LD114.3 (R), U10.39 (OUTG14)
/LEDs/led114r: LD114.2 (R), U10.40 (OUTR14)
/LEDs/led115b: LD115.4 (R), U11.4 (OUTB4)
/LEDs/led115g: LD115.3 (R), U11.6 (OUTG4)
/LEDs/led115r: LD115.2 (R), U11.5 (OUTR4)
/LEDs/led116b: LD116.4 (R), U11.7 (OUTB0)
/LEDs/led116g: LD116.3 (R), U11.9 (OUTG0)
/LEDs/led116r: LD116.2 (R), U11.8 (OUTR0)
/LEDs/led117b: LD117.4 (R), U11.10 (OUTB5)
/LEDs/led117g: LD117.3 (R), U11.12 (OUTG5)
/LEDs/led117r: LD117.2 (R), U11.11 (OUTR5)
/LEDs/led118b: LD118.4 (R), U11.13 (OUTB1)
/LEDs/led118g: LD118.3 (R), U11.15 (OUTG1)
/LEDs/led118r: LD118.2 (R), U11.14 (OUTR1)
/LEDs/led119b: LD119.4 (R), U10.25 (OUTB7)
/LEDs/led119g: LD119.3 (R), U10.27 (OUTG7)
/LEDs/led119r: LD119.2 (R), U10.26 (OUTR7)
/LEDs/led120b: LD120.4 (R), U10.22 (OUTB3)
/LEDs/led120g: LD120.3 (R), U10.24 (OUTG3)
/LEDs/led120r: LD120.2 (R), U10.23 (OUTR3)
/LEDs/led121b: LD121.4 (R), U14.16 (OUTB2)
/LEDs/led121g: LD121.3 (R), U14.18 (OUTG2)
/LEDs/led121r: LD121.2 (R), U14.17 (OUTR2)
/LEDs/led122b: LD122.4 (R), U14.22 (OUTB3)
/LEDs/led122g: LD122.3 (R), U14.24 (OUTG3)
/LEDs/led122r: LD122.2 (R), U14.23 (OUTR3)
/LEDs/led123b: LD123.4 (R), U15.10 (OUTB5)
/LEDs/led123g: LD123.3 (R), U15.12 (OUTG5)
/LEDs/led123r: LD123.2 (R), U15.11 (OUTR5)
/LEDs/led124b: LD124.4 (R), U15.13 (OUTB1)
/LEDs/led124g: LD124.3 (R), U15.15 (OUTG1)
/LEDs/led124r: LD124.2 (R), U15.14 (OUTR1)
/LEDs/led125b: LD125.4 (R), U11.47 (OUTB9)
/LEDs/led125g: LD125.3 (R), U11.45 (OUTG9)
/LEDs/led125r: LD125.2 (R), U11.46 (OUTR9)
/LEDs/led126b: LD126.4 (R), U11.44 (OUTB13)
/LEDs/led126g: LD126.3 (R), U11.42 (OUTG13)
/LEDs/led126r: LD126.2 (R), U11.43 (OUTR13)
/LEDs/led127b: LD127.4 (R), U11.41 (OUTB14)
/LEDs/led127g: LD127.3 (R), U11.39 (OUTG14)
/LEDs/led127r: LD127.2 (R), U11.40 (OUTR14)
/LEDs/led128b: LD128.4 (R), U11.50 (OUTB12)
/LEDs/led128g: LD128.3 (R), U11.48 (OUTG12)
/LEDs/led128r: LD128.2 (R), U11.49 (OUTR12)
/LEDs/led129b: LD129.4 (R), U11.53 (OUTB8)
/LEDs/led129g: LD129.3 (R), U11.51 (OUTG8)
/LEDs/led129r: LD129.2 (R), U11.52 (OUTR8)
/LEDs/led130b: LD130.4 (R), U11.16 (OUTB2)
/LEDs/led130g: LD130.3 (R), U11.18 (OUTG2)
/LEDs/led130r: LD130.2 (R), U11.17 (OUTR2)
/LEDs/led131b: LD131.4 (R), U11.19 (OUTB6)
/LEDs/led131g: LD131.3 (R), U11.21 (OUTG6)
/LEDs/led131r: LD131.2 (R), U11.20 (OUTR6)
/LEDs/led132b: LD132.4 (R), U11.22 (OUTB3)
/LEDs/led132g: LD132.3 (R), U11.24 (OUTG3)
/LEDs/led132r: LD132.2 (R), U11.23 (OUTR3)
/LEDs/led133b: LD133.4 (R), U11.25 (OUTB7)
/LEDs/led133g: LD133.3 (R), U11.27 (OUTG7)
/LEDs/led133r: LD133.2 (R), U11.26 (OUTR7)
/LEDs/led134b: LD134.4 (R), U14.10 (OUTB5)
/LEDs/led134g: LD134.3 (R), U14.12 (OUTG5)
/LEDs/led134r: LD134.2 (R), U14.11 (OUTR5)
/LEDs/led135b: LD135.4 (R), U14.13 (OUTB1)
/LEDs/led135g: LD135.3 (R), U14.15 (OUTG1)
/LEDs/led135r: LD135.2 (R), U14.14 (OUTR1)
/LEDs/led136b: LD136.4 (R), U15.16 (OUTB2)
/LEDs/led136g: LD136.3 (R), U15.18 (OUTG2)
/LEDs/led136r: LD136.2 (R), U15.17 (OUTR2)
/LEDs/led137b: LD137.4 (R), U15.19 (OUTB6)
/LEDs/led137g: LD137.3 (R), U15.21 (OUTG6)
/LEDs/led137r: LD137.2 (R), U15.20 (OUTR6)
/LEDs/led138b: LD138.4 (R), U11.38 (OUTB10)
/LEDs/led138g: LD138.3 (R), U11.36 (OUTG10)
/LEDs/led138r: LD138.2 (R), U11.37 (OUTR10)
/LEDs/led139b: LD139.4 (R), U11.35 (OUTB15)
/LEDs/led139g: LD139.3 (R), U11.33 (OUTG15)
/LEDs/led139r: LD139.2 (R), U11.34 (OUTR15)
/LEDs/led140b: LD140.4 (R), U11.32 (OUTB11)
/LEDs/led140g: LD140.3 (R), U11.30 (OUTG11)
/LEDs/led140r: LD140.2 (R), U11.31 (OUTR11)
/LEDs/led141b: LD141.4 (R), U12.53 (OUTB8)
/LEDs/led141g: LD141.3 (R), U12.51 (OUTG8)
/LEDs/led141r: LD141.2 (R), U12.52 (OUTR8)
/LEDs/led142b: LD142.4 (R), U12.16 (OUTB2)
/LEDs/led142g: LD142.3 (R), U12.18 (OUTG2)
/LEDs/led142r: LD142.2 (R), U12.17 (OUTR2)
/LEDs/led143b: LD143.4 (R), U12.13 (OUTB1)
/LEDs/led143g: LD143.3 (R), U12.15 (OUTG1)
/LEDs/led143r: LD143.2 (R), U12.14 (OUTR1)
/LEDs/led144b: LD144.4 (R), U12.10 (OUTB5)
/LEDs/led144g: LD144.3 (R), U12.12 (OUTG5)
/LEDs/led144r: LD144.2 (R), U12.11 (OUTR5)
/LEDs/led145b: LD145.4 (R), U12.7 (OUTB0)
/LEDs/led145g: LD145.3 (R), U12.9 (OUTG0)
/LEDs/led145r: LD145.2 (R), U12.8 (OUTR0)
/LEDs/led146b: LD146.4 (R), U12.4 (OUTB4)
/LEDs/led146g: LD146.3 (R), U12.6 (OUTG4)
/LEDs/led146r: LD146.2 (R), U12.5 (OUTR4)
/LEDs/led147b: LD147.4 (R), U14.4 (OUTB4)
/LEDs/led147g: LD147.3 (R), U14.6 (OUTG4)
/LEDs/led147r: LD147.2 (R), U14.5 (OUTR4)
/LEDs/led148b: LD148.4 (R), U14.7 (OUTB0)
/LEDs/led148g: LD148.3 (R), U14.9 (OUTG0)
/LEDs/led148r: LD148.2 (R), U14.8 (OUTR0)
/LEDs/led149b: LD149.4 (R), U15.22 (OUTB3)
/LEDs/led149g: LD149.3 (R), U15.24 (OUTG3)
/LEDs/led149r: LD149.2 (R), U15.23 (OUTR3)
/LEDs/led150b: LD150.4 (R), U15.25 (OUTB7)
/LEDs/led150g: LD150.3 (R), U15.27 (OUTG7)
/LEDs/led150r: LD150.2 (R), U15.26 (OUTR7)
/LEDs/led151b: LD151.4 (R), U12.50 (OUTB12)
/LEDs/led151g: LD151.3 (R), U12.48 (OUTG12)
/LEDs/led151r: LD151.2 (R), U12.49 (OUTR12)
/LEDs/led152b: LD152.4 (R), U12.47 (OUTB9)
/LEDs/led152g: LD152.3 (R), U12.45 (OUTG9)
/LEDs/led152r: LD152.2 (R), U12.46 (OUTR9)
/LEDs/led153b: LD153.4 (R), U12.44 (OUTB13)
/LEDs/led153g: LD153.3 (R), U12.42 (OUTG13)
/LEDs/led153r: LD153.2 (R), U12.43 (OUTR13)
/LEDs/led154b: LD154.4 (R), U12.41 (OUTB14)
/LEDs/led154g: LD154.3 (R), U12.39 (OUTG14)
/LEDs/led154r: LD154.2 (R), U12.40 (OUTR14)
/LEDs/led155b: LD155.4 (R), U13.47 (OUTB9)
/LEDs/led155g: LD155.3 (R), U13.45 (OUTG9)
/LEDs/led155r: LD155.2 (R), U13.46 (OUTR9)
/LEDs/led156b: LD156.4 (R), U13.4 (OUTB4)
/LEDs/led156g: LD156.3 (R), U13.6 (OUTG4)
/LEDs/led156r: LD156.2 (R), U13.5 (OUTR4)
/LEDs/led157b: LD157.4 (R), U13.7 (OUTB0)
/LEDs/led157g: LD157.3 (R), U13.9 (OUTG0)
/LEDs/led157r: LD157.2 (R), U13.8 (OUTR0)
/LEDs/led158b: LD158.4 (R), U13.10 (OUTB5)
/LEDs/led158g: LD158.3 (R), U13.12 (OUTG5)
/LEDs/led158r: LD158.2 (R), U13.11 (OUTR5)
/LEDs/led159b: LD159.4 (R), U13.13 (OUTB1)
/LEDs/led159g: LD159.3 (R), U13.15 (OUTG1)
/LEDs/led159r: LD159.2 (R), U13.14 (OUTR1)
/LEDs/led160b: LD160.4 (R), U12.25 (OUTB7)
/LEDs/led160g: LD160.3 (R), U12.27 (OUTG7)
/LEDs/led160r: LD160.2 (R), U12.26 (OUTR7)
/LEDs/led161b: LD161.4 (R), U12.22 (OUTB3)
/LEDs/led161g: LD161.3 (R), U12.24 (OUTG3)
/LEDs/led161r: LD161.2 (R), U12.23 (OUTR3)
/LEDs/led162b: LD162.4 (R), U12.19 (OUTB6)
/LEDs/led162g: LD162.3 (R), U12.21 (OUTG6)
/LEDs/led162r: LD162.2 (R), U12.20 (OUTR6)
/LEDs/led163b: LD163.4 (R), U12.38 (OUTB10)
/LEDs/led163g: LD163.3 (R), U12.36 (OUTG10)
/LEDs/led163r: LD163.2 (R), U12.37 (OUTR10)
/LEDs/led164b: LD164.4 (R), U12.35 (OUTB15)
/LEDs/led164g: LD164.3 (R), U12.33 (OUTG15)
/LEDs/led164r: LD164.2 (R), U12.34 (OUTR15)
/LEDs/led165b: LD165.4 (R), U12.32 (OUTB11)
/LEDs/led165g: LD165.3 (R), U12.30 (OUTG11)
/LEDs/led165r: LD165.2 (R), U12.31 (OUTR11)
/LEDs/led166b: LD166.4 (R), U13.44 (OUTB13)
/LEDs/led166g: LD166.3 (R), U13.42 (OUTG13)
/LEDs/led166r: LD166.2 (R), U13.43 (OUTR13)
/LEDs/led167b: LD167.4 (R), U13.16 (OUTB2)
/LEDs/led167g: LD167.3 (R), U13.18 (OUTG2)
/LEDs/led167r: LD167.2 (R), U13.17 (OUTR2)
/LEDs/led168b: LD168.4 (R), U13.22 (OUTB3)
/LEDs/led168g: LD168.3 (R), U13.24 (OUTG3)
/LEDs/led168r: LD168.2 (R), U13.23 (OUTR3)
/LEDs/led169b: LD169.4 (R), U13.19 (OUTB6)
/LEDs/led169g: LD169.3 (R), U13.21 (OUTG6)
/LEDs/led169r: LD169.2 (R), U13.20 (OUTR6)
/LEDs/led170b: LD170.4 (R), U14.53 (OUTB8)
/LEDs/led170g: LD170.3 (R), U14.51 (OUTG8)
/LEDs/led170r: LD170.2 (R), U14.52 (OUTR8)
/LEDs/led171b: LD171.4 (R), U14.44 (OUTB13)
/LEDs/led171g: LD171.3 (R), U14.42 (OUTG13)
/LEDs/led171r: LD171.2 (R), U14.43 (OUTR13)
/LEDs/led172b: LD172.4 (R), U15.47 (OUTB9)
/LEDs/led172g: LD172.3 (R), U15.45 (OUTG9)
/LEDs/led172r: LD172.2 (R), U15.46 (OUTR9)
/LEDs/led173b: LD173.4 (R), U15.38 (OUTB10)
/LEDs/led173g: LD173.3 (R), U15.36 (OUTG10)
/LEDs/led173r: LD173.2 (R), U15.37 (OUTR10)
/LEDs/led174b: LD174.4 (R), U13.53 (OUTB8)
/LEDs/led174g: LD174.3 (R), U13.51 (OUTG8)
/LEDs/led174r: LD174.2 (R), U13.52 (OUTR8)
/LEDs/led175b: LD175.4 (R), U13.41 (OUTB14)
/LEDs/led175g: LD175.3 (R), U13.39 (OUTG14)
/LEDs/led175r: LD175.2 (R), U13.40 (OUTR14)
/LEDs/led176b: LD176.4 (R), U13.38 (OUTB10)
/LEDs/led176g: LD176.3 (R), U13.36 (OUTG10)
/LEDs/led176r: LD176.2 (R), U13.37 (OUTR10)
/LEDs/led177b: LD177.4 (R), U13.25 (OUTB7)
/LEDs/led177g: LD177.3 (R), U13.27 (OUTG7)
/LEDs/led177r: LD177.2 (R), U13.26 (OUTR7)
/LEDs/led178b: LD178.4 (R), U14.50 (OUTB12)
/LEDs/led178g: LD178.3 (R), U14.48 (OUTG12)
/LEDs/led178r: LD178.2 (R), U14.49 (OUTR12)
/LEDs/led179b: LD179.4 (R), U14.41 (OUTB14)
/LEDs/led179g: LD179.3 (R), U14.39 (OUTG14)
/LEDs/led179r: LD179.2 (R), U14.40 (OUTR14)
/LEDs/led180b: LD180.4 (R), U14.35 (OUTB15)
/LEDs/led180g: LD180.3 (R), U14.33 (OUTG15)
/LEDs/led180r: LD180.2 (R), U14.34 (OUTR15)
/LEDs/led181b: LD181.4 (R), U15.53 (OUTB8)
/LEDs/led181g: LD181.3 (R), U15.51 (OUTG8)
/LEDs/led181r: LD181.2 (R), U15.52 (OUTR8)
/LEDs/led182b: LD182.4 (R), U15.44 (OUTB13)
/LEDs/led182g: LD182.3 (R), U15.42 (OUTG13)
/LEDs/led182r: LD182.2 (R), U15.43 (OUTR13)
/LEDs/led183b: LD183.4 (R), U15.35 (OUTB15)
/LEDs/led183g: LD183.3 (R), U15.33 (OUTG15)
/LEDs/led183r: LD183.2 (R), U15.34 (OUTR15)
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
